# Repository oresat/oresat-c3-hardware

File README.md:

# oresat-c3
## General information
This is the C3 (Command, Communication, and Control) card for OreSat. It acts as the central control point for the entire OreSat project, provides
telemetry to the ground, and receiver commands. It's the "on board computer" (OBC) of the OreSat bus. It has:

- Octavo OSD335x-SM SIP AM335X-based Cortex A8 Microporcessor
- On Semi AX5043-based L Band (1.265 GHz) receiver
- On Semi AX5043-based UHF Band (436.5 MHz) receiver and transmitter with 1W PA.
- Custom radiation tolerant watchdog timer based on the TI TLV1042 comparator.
- 16 GB eMMC flash data storage
- 1 Mbit of FRAM for high reliability state and variable storage
- Supercapacitor-backed up RTC
- Two antenna deployment circuits
- OreSat Power Domain (OPD) control circuitry

Design materials are on Google docs; we'll post links / PDFs soon.

Bill of Materials (BOM) can be found [here](https://docs.google.com/spreadsheets/d/11vG1kWyrAjmbF5QJM-EhXmvQoF6O47japwYlHF802do/edit#gid=1239769296).

## OreSat C3 version 6 (KiCAD)

Fixes for the radio receivers, version 2 backplane pinout, and lots of little tweaks
after our lessons learned on OreSat0. OH, and a COMPLETE REFACTOR since we switched from
the STM32F439 to an Octavo OSD335x-SM and switched from EAGLE to KICAD. Yikes.

### V6 Software

The C3 runs Python code that interacts with the radios, peripherals, and CAN bus. [Here's more information](https://github.com/oresat/oresat-c3-software).

## OreSat C3 version 5 (EAGLE)

C3 V5 flew on Oresat0, Oregon's first satellite! Everything worked great, except for the
radio receivers (L band LNA oscillated, and UHF LNA was turned off in firmware).

### v5 Firmware

The firmware for the C3 card is written in C and runs on top of ChibiOS, a small RTOS.
It is integrated into the [oresat-firmware](https://github.com/oresat/oresat-firmware) repository.
The firmware application for this project is located
[here](https://github.com/oresat/oresat-firmware/tree/c3_capstone/src/f4/app_c3_v1).

## OreSat C3 version 4 (EAGLE)

C3 V4 is our latest version of the C3 card; it's getting ready for flight in 
Q2 2021 in OreSat0. It's got all of the functionality necessary for flight.

## OreSat C3 V3 (2019-2020 ECE Capstone)

The 2018-2019 ECE Capstone brought the card to version 3. It implements an
STM32F446VET6 IC, the full L band receiver with ultistage LNA, and a UHF radio 
with LNA but no PA for transmitting.

## Breadboard Prototype

Most embedded project starts out as a bunch of development boards strung together;
the C3 is no different! The breadboard prototype for the C3 card implements an
STM32F446RE development board connected to two SPI radios, the OreSat
FlatSat backplane via a CAN transceiver and I2C for the OPD interface,
and a SDIO and SPI connected SD/MMC Card. The breadboard implements
stronger pullups for the I2C lines than the GPIO of the STM32 can
provide. It is currently capable of interfacing with and activating the
OPD connected boards.

## License

All materials in this repo are copyright Portland State Aerospace Society and are licensed under the CERN Open Hardware Licence Version 2 -
Strongly Reciprocal (CERN-OHL-S v2), or any later version. A copy of the license is located in [here](LICENSE.md).

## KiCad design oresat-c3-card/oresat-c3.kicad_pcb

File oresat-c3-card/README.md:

---
title: "**OreSat C3 Card**"
subtitle: |
  **Fabrication and Assembly Information**\
  For build TIME-STAMP
fontsize: 10pt
geometry:
  - margin=0.5in
toc: true
toc-depth: 2
colorlinks: true
urlcolor: blue
---

\newpage

# About this Board

## Board Description

The C3 ("Command, Control, and Communications") card is the main on-board computer (OBC) / housekeeping unit (HKU) / Command and Data Handling (CDH) subsystem for the open source [OreSat CubeSat system](https://www.oresat.org/). The C3 card:

- Connects to the backplane with a main connector and two RF ports
- Has an L band radio receiver based on the AT86RF215.
- Has a UHF radio transceiver based on the AT86RF215
- Has a radiation tolerant watchdog timer (with a cheap commercial replacement if you're not going to orbit)
- Controls the OreSat Power Domain (OPD), which turns on and off and controls other cards
- Talks to both CAN OreSat CAN busses

## Documentation Links

- C3 hardware Git repository: <https://github.com/oresat/oresat-c3-hardware>
- C3 software Git reposity: <https://github.com/oresat/oresat-c3-software>
- **TODO:** C3 Design Notes + Design Review Notes

## Documentation Files

| Filename                        | Notes                                    |
| ------------------------------- | ---------------------------------------- |
| README.pdf                      | This README file                         |
| PROJECT-NAME-outline.dxf        | Board outline (with holes) in DXF format |
| PROJECT-NAME-pcba.step          | 3D model of PCBA (with components)       |
| PROJECT-NAME-render-bot.jpg     | Render of the top of the 3D model        |
| PROJECT-NAME-render-bot.jpg     | Render of the bottom of the 3D model     |
| PROJECT-NAME-schematic.pdf      | PDF of board schematics                  |

## Contact Information

- Website: <https://www.oresat.org/>
- Email: <oresat@pdx.edu>
- Instagram: @pdxaerospace

## Board Renders

{width=50%}
{width=50%}

\newpage

# Printed Circuit Board (PCB) Fabrication Information

## Board Info

- 4 layer board
- Bounding box is 99.8 x 94.6 mm (3.93 x 3.72 in)
- Board thickness is 1.59 mm (0.063 inch)
- **Important:** See Materials and Stack Up sections below

## Board Requirements

- Design Rules
    - Minimum Trace / Space design rules
       - Outer layers: 0.127 mm (5.0 mil) / 0.127 mm (5.0 mil)
       - Inner layers: 0.127 mm (5.0 mil) / 0.127 mm (5.0 mil)
    - Outer dimension router tolerance: +/- 0.254 mm (10.0 mil)
    - Hole placement tolerance: +/- 0.075 mm (3.0 mil)
    - Inner tab routed slot tolerance: +/- 0.254 mm (10.0 mil)
- Drills
   - Drill Positional Tolerance: 0.051 mm (2.0 mil)
   - Drill Size tolerance: +/- 0.064 mm (2.5 mil)
- Plated/Un-plated holes
  - There are 6 un-plated (NPT) holes
  - There are 1477 plated through (PTH) holes
  - PTH minimum diameter: 0.254 mm (10 mil)
  - PTH minimum annulus: 0.102 mm (4 mil) radius
- Outline/Routing
  - Requires a 1.0 mm or smaller diameter routing bit
- Slots
  - There are no slots.
- Cutouts
  - There are no cutouts
- There are 3 fiducials on the top layer.
- Panel tabs ("mouse bites")
   - Card edges must be smooth; no mouse bites or other intrusions into the card outline.
   - If external mouse bites are required, minimize and customer will remove by hand before assembly.
- If not otherwise specified, build to IPC 6012 Class 2 or better.

## Materials

- Controlled impedance
   - The stackup is critical for the performance of high speed signals on this board.
   - As long as the stackup is controlled, the board is not considered controlled impedance.
- Isola FR408HR or material with equivalent Dk.
- Board Surface treatment should be ENIG, althogh immersion Silver is acceptable.
- White silkscreen on top and bottom surface
- Taiyo PSR-4000 or equivalent soldermask on top and bottom, no requirements for color.

## Stack Up

| Layer         | Thickness           | Notes                                        |
|---------------|---------------------|----------------------------------------------|
| Top Copper    | 0.043 mm /  1.7 mil |  Layer 1 foil, 1 oz Cu after plating         |
| prepreg       | 0.200 mm /  7.9 mil |  Prepreg - Isola FR408HR 2113                |
| Layer 2       | 0.018 mm /  0.7 mil |  Layer 2 foil, 0.5 oz Cu                     |
| Core          | 0.991 mm /   39 mil |  Core Isola FR408HR                          |
| Layer 3       | 0.018 mm /  0.7 mil |  Layer 3 foil, 0.5 oz Cu                     |
| prepreg       | 0.200 mm /  7.9 mil |  Prepreg - Isola FR408HR 2113                |
| Bottom Copper | 0.043 mm /  1.7 mil |  Layer 4 foil, 1 oz copper after plating     |
| **Total Stackup** | **1.588 mm / 62.5 mil** |                                      |

## Array / Panel Information

- Coordinate with Contract Manufacturer (CM) for optimal size of this panel.
- If no feedback from CM, then produce single boards (no panel).

## Fabrication Files

### IPC-2581 File

| Filename                 | Notes                                   |
| ------------------------ | --------------------------------------- |
| PROJECT-NAME-ipc2581.xml | IPC-2581 board information file         |

### Legacy PCB Files

| Filename                      | Notes                                         |
| ------------------------------| --------------------------------------------- |
| PROJECT-NAME-Edge_Cuts.gbr    | RS274X file for the dimension (outline) layer |
| PROJECT-NAME-F_Silkscreen.gbr | RS274X file for the top silkscreen            |
| PROJECT-NAME-F_Mask.gbr       | RS274X file for the top soldermask            |
| PROJECT-NAME-F_Cu.gbr         | RS274X file for the top copper layer          |
| PROJECT-NAME-In1_Cu.gbr       | RS274X file for the layer 2 copper            |
| PROJECT-NAME-In2_Cu.gbr       | RS274X file for the layer 3 copper            |
| PROJECT-NAME-B_Cu.gbr         | RS274X file for the bottom copper layer       |
| PROJECT-NAME-B_Mask.gbr       | RS274X file for the bottom soldermask         |
| PROJECT-NAME-B_Silkscreen.gbr | RS274X file for the bottom silkscreen         |
| PROJECT-NAME-NPTH.drl         | Excellon file for non-plated through holes    |
| PROJECT-NAME-PTH.drl          | Excellon file for plated through holes        | 

\newpage

# Printed Circuit Board Assembly (PCBA) Information

## Assembly Info

- All components are on the top side of the board.
- This PCBA is mostly surface mount (SMT) with a few (THT) components.

## Assembly Requirements

- Assemble to IPC Class 2 or better
- Bake components that are not moisture sealed to appropriate levels as required.
- Solder paste MUST be leaded.
- Aqueous flux and wash strongly preferred.
   - Clean to NASA Standard "Visibly Clean (VC)": No particles or residues are visible to the naked eye.
- No conformal coating.
- Ship in antistatic protective bag

## Component Specific Assembly Information

- SMPM connectors (J3, J4) should be hand-added (there is no solder paste for their footprints).
- U1 and U28 are extremely expensive ($75 and $150 ea, respectively).
- U15 and U21 are EOL and will be supplied in cut tape form.

## Assembly Files

### IPC-2581 File

| Filename                 | Notes                           |
| ------------------------ | ------------------------------- |
| PROJECT-NAME-ipc2581.xml | IPC-2581 board information file |

### Bill of Materials (BOM)

| Filename             | Description                            |
| -------------------- | -------------------------------------- |
| PROJECT-NAME-bom.csv | BOM in Comma Separated Variable format |

### Solder Paste Stencils

| Filename                 | Notes                                            |
| ------------------------ | ------------------------------------------------ |
| PROJECT-NAME-B_Paste.gbr | RS274X file for top/front solder paste stencil   |
| PROJECT-NAME-F_Paste.gbr | RS274X file for bottom/back solder paste stencil |

### Mounting/Placement Location

| Filename            | Description                                 |
| ------------------- | ------------------------------------------- |
| PROJECT-NAME-3u.pos | Pick and place locations for components     |

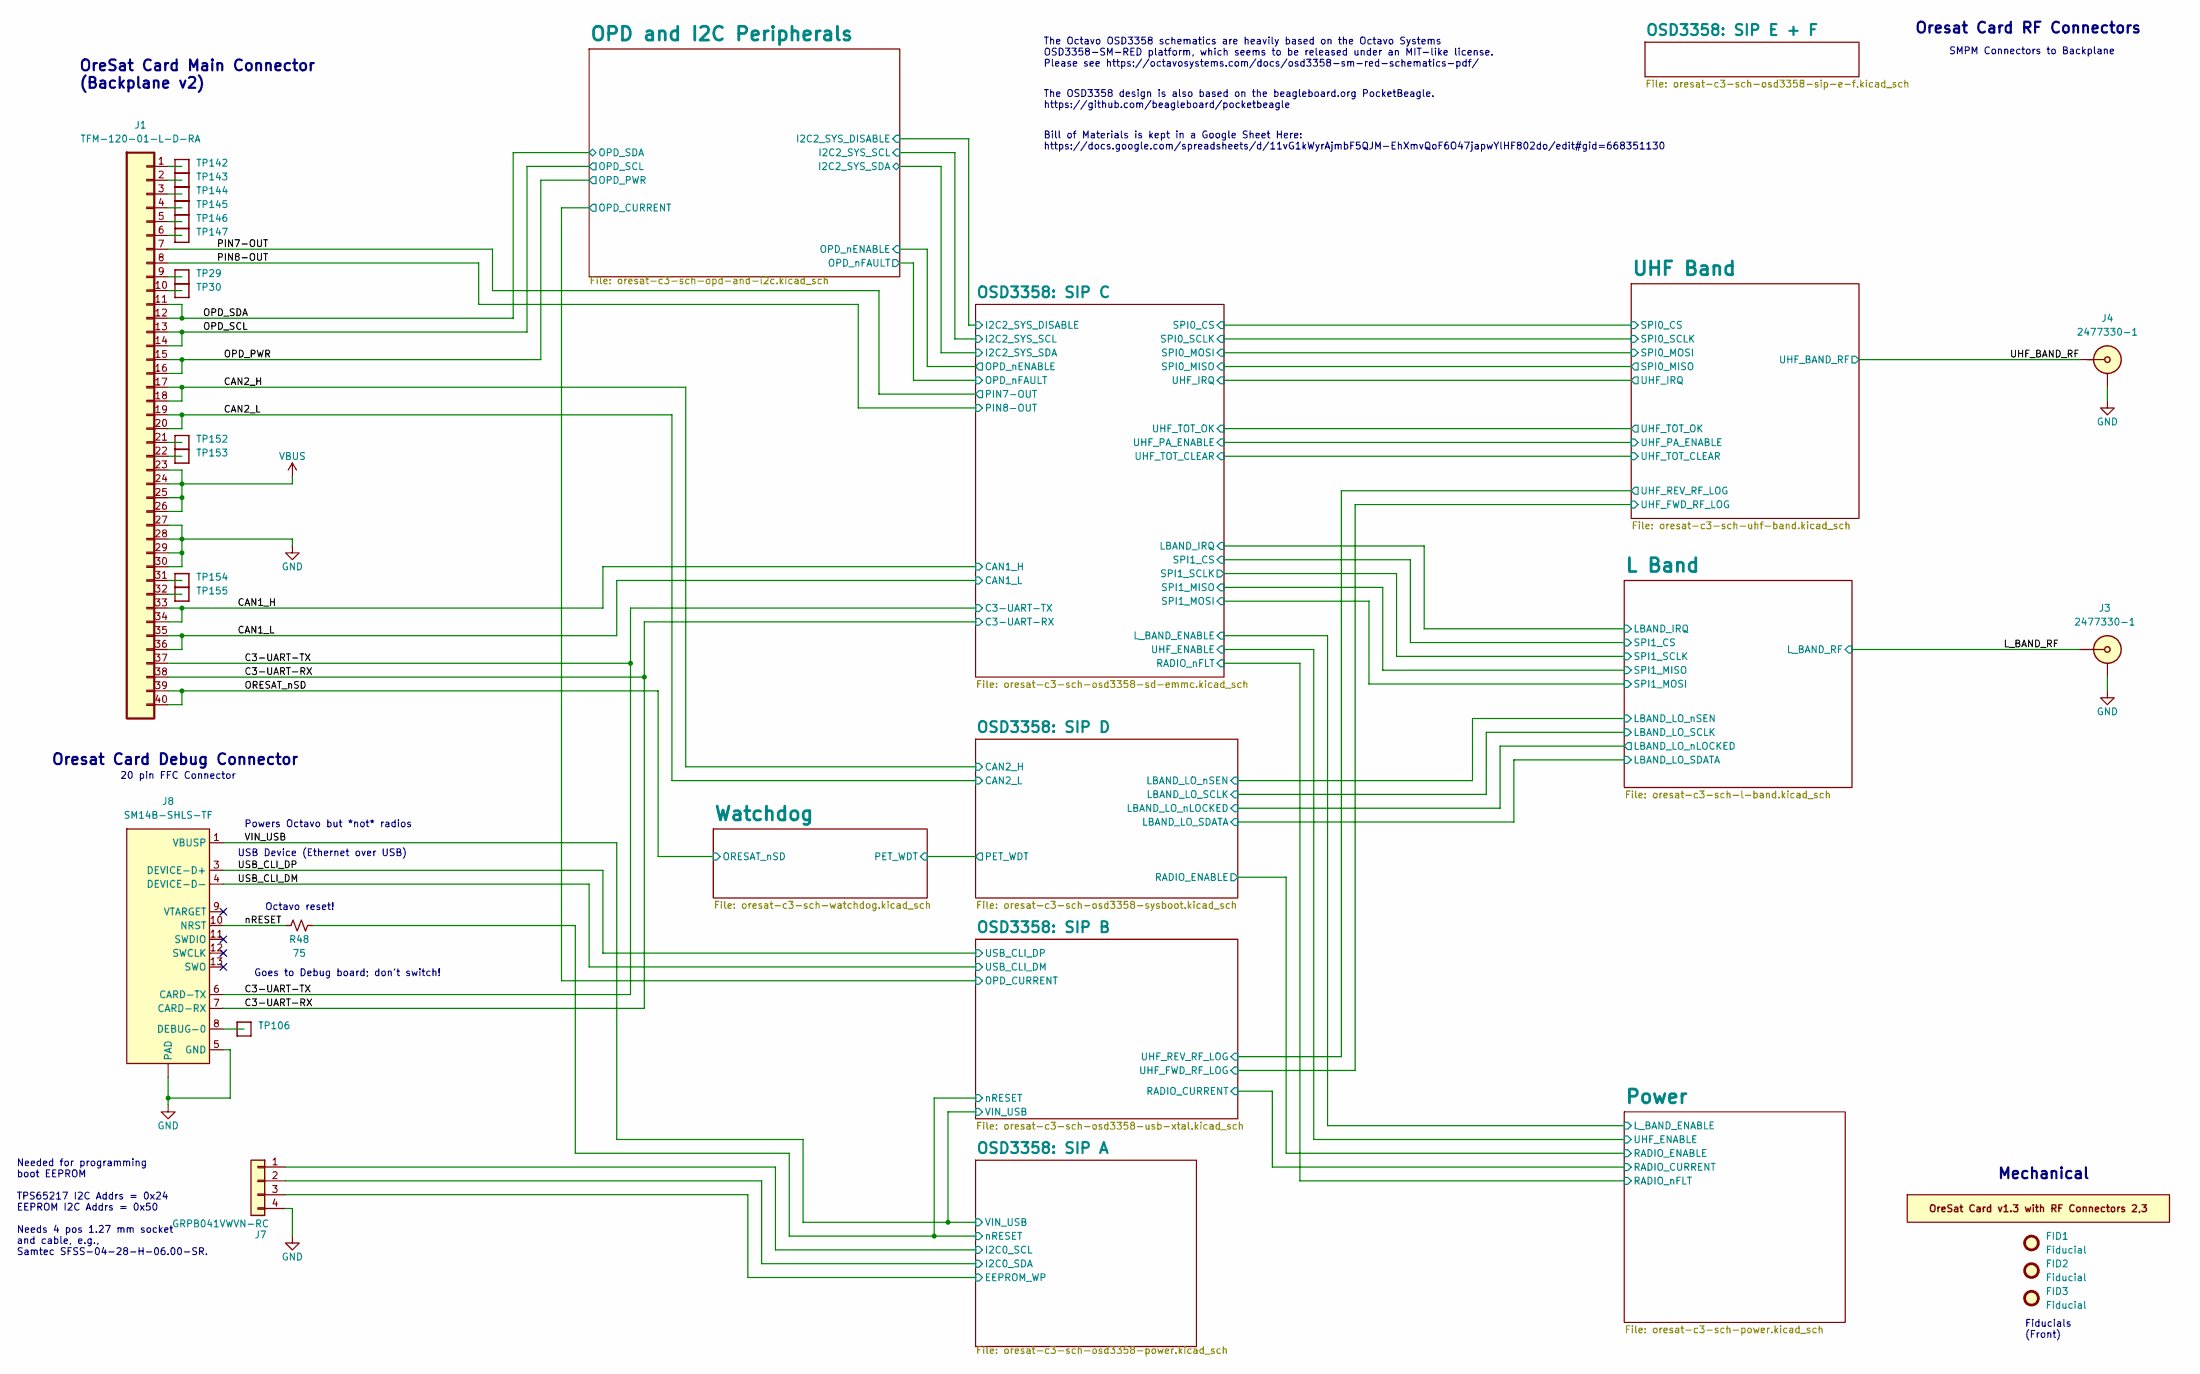
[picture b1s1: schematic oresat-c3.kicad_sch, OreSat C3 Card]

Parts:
FID1, FID2, FID3: Fiducial; Fiducial_1mm_Mask2mm
J1: TFM-120-01-L-D-RA; J-SAMTEC-TFM-120-X1-XXX-D-RA; MPN TFM-120-01-L-D-RA
J3, J4: 2477330-1; J-MOLEX-SMPM-073300-002X; MPN 2477330-1
J7: GRPB041VWVN-RC; PinHeader_1x04_P1.27mm_Vertical; MPN GRPB041VWVN-RC
J8: SM14B-SHLS-TF; J-JST-SM14BSHLSTF; MPN SM14B-SHLS-TF
PCB1: ORESAT-CARD-V1.3-GENERIC-1RF-POS2; ORESAT-CARD-V1.3-2RF-RIGHT; MPN N/A
R48: 75; 0603-C-NOSILK; MPN RMCF0603FT75R0
TP29, TP30, TP106, TP142, TP143, TP144, TP145, TP146, TP147, TP152, TP153, TP154, TP155: Test-Point; TestPoint_Pad_D1.0mm

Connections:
/C3-UART-RX: J1.38, J8.7 (CARD-RX); also elsewhere on the board
/C3-UART-TX: J1.37, J8.6 (CARD-TX); also elsewhere on the board
/CAN1_H: J1.33, J1.34; also elsewhere on the board
/CAN1_L: J1.35, J1.36; also elsewhere on the board
/CAN2_H: J1.17, J1.18; also elsewhere on the board
/CAN2_L: J1.19, J1.20; also elsewhere on the board
/L_BAND_RF: J3.1 (SIG_SIG); also elsewhere on the board
/OPD_PWR: J1.15, J1.16; also elsewhere on the board
/OPD_SCL: J1.13, J1.14; also elsewhere on the board
/OPD_SDA: J1.11, J1.12; also elsewhere on the board
/ORESAT_nSD: J1.39, J1.40; also elsewhere on the board
/OSD3358: SIP A/EEPROM_WP: J7.3; also elsewhere on the board
/OSD3358: SIP A/I2C0_SCL: J7.1; also elsewhere on the board
/OSD3358: SIP A/I2C0_SDA: J7.2; also elsewhere on the board
/OSD3358: SIP A/nRESET: R48.2; also elsewhere on the board
/PIN7-OUT: J1.7; also elsewhere on the board
/PIN8-OUT: J1.8; also elsewhere on the board
/UHF_BAND_RF: J4.1 (SIG_SIG); also elsewhere on the board
/USB_CLI_DM: J8.4 (DEVICE-D-); also elsewhere on the board
/USB_CLI_DP: J8.3 (DEVICE-D+); also elsewhere on the board
/VIN_USB: J8.1 (VBUSP), J8.2 (VBUSP); also elsewhere on the board
/nRESET: J8.10 (NRST), R48.1
GND: J1.27, J1.28, J1.29, J1.30, J3.2 (SHLD_SHLD), J3.SHLD, J4.2 (SHLD_SHLD), J4.SHLD, J7.4, J8.5 (GND), J8.14 (GND), J8.15 (PAD), J8.16 (PAD); also elsewhere on the board
unnamed: J1.1, TP142.1 (1_1)
unnamed: J1.2, TP143.1 (1_1)
unnamed: J1.3, TP144.1 (1_1)
unnamed: J1.4, TP145.1 (1_1)
unnamed: J1.5, TP146.1 (1_1)
unnamed: J1.6, TP147.1 (1_1)
unnamed: J1.9, TP29.1 (1_1)
unnamed: J1.10, TP30.1 (1_1)
unnamed: J1.21, TP152.1 (1_1)
unnamed: J1.22, TP153.1 (1_1)
unnamed: J1.31, TP154.1 (1_1)
unnamed: J1.32, TP155.1 (1_1)
unnamed: J8.8 (DEBUG-0), TP106.1 (1_1)
VBUS: J1.23, J1.24, J1.25, J1.26; also elsewhere on the board

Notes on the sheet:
Bill of Materials is kept in a Google Sheet Here: https://docs.google.com/spreadsheets/d/11vG1kWyrAjmbF5QJM-EhXmvQoF6O47japwYlHF802do/edit#gid=668351130
The Octavo OSD3358 schematics are heavily based on the Octavo Systems OSD3358-SM-RED platform, which seems to be released under an MIT-like license. Please see https://octavosystems.com/docs/osd3358-sm-red-schematics-pdf/
OreSat Card Main Connector (Backplane v2)
Mechanical
Needed for programming boot EEPROM TPS65217 I2C Addrs = 0x24 EEPROM I2C Addrs = 0x50 Needs 4 pos 1.27 mm socket and cable, e.g., Samtec SFSS-04-28-H-06.00-SR.
Octavo reset!
20 pin FFC Connector
Oresat Card RF Connectors
Oresat Card Debug Connector
Goes to Debug board; don't switch!
Powers Octavo but *not* radios
The OSD3358 design is also based on the beagleboard.org PocketBeagle. https://github.com/beagleboard/pocketbeagle
USB Device (Ethernet over USB)
SMPM Connectors to Backplane
Fiducials (Front)

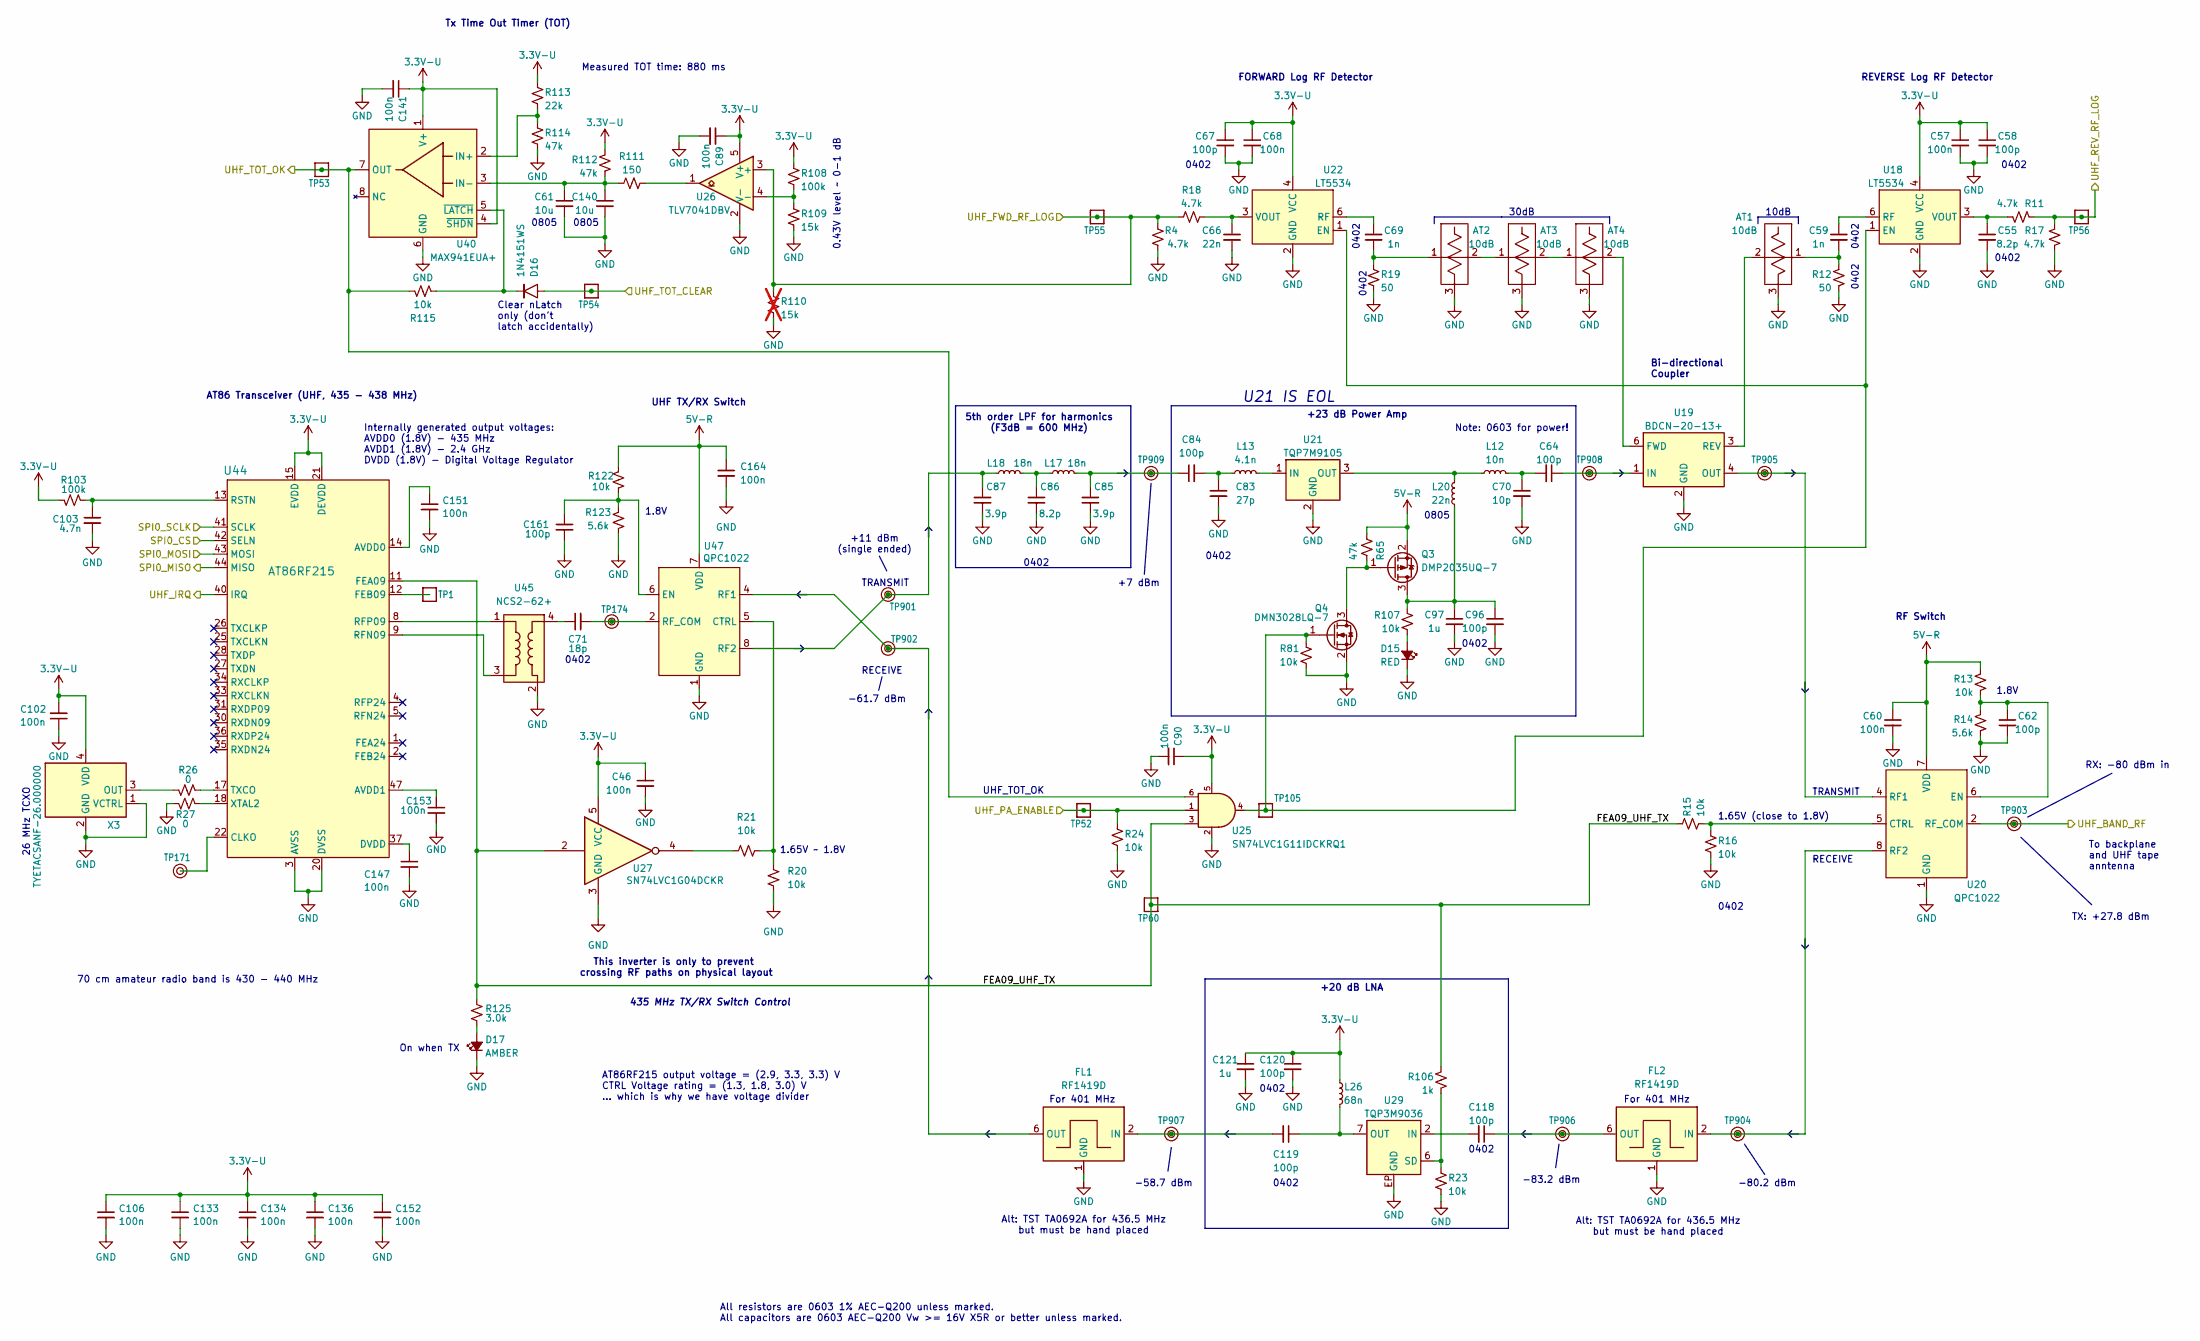
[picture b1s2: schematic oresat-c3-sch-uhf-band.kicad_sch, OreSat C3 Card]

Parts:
AT1, AT2, AT3, AT4: 10dB; PAT0816(0603); MPN PAT0816-C-10DB-T5
C46, C57, C60, C68, C89, C90, C102, C106, C133, C134, C136, C141, C147, C151, C152, C153, C164: 100n; 0603-C-NOSILK; MPN C0603C104K5RACAUTO
C55, C86: 8.2p; 0402-B-NOSILK; MPN GCQ1555C1H8R2BB01D
C58, C67, C84, C96, C118, C119, C120: 100p; 0402-B-NOSILK; MPN C0402C101J5GACAUTO
C59, C69: 1n; 0402-B-NOSILK; MPN C0402C102J3GACAUTO
C61, C140: 10u; 0805-C-NOSILK; MPN GRT21BC71E106KE13K
C62, C64, C161: 100p; 0603-C-NOSILK; MPN C0603C101K5HACAUTO
C66: 22n; 0603-C-NOSILK; MPN C0603C223K1RACAUTO
C70: 10p; 0603-C-NOSILK; MPN C0603C100J1GACAUTO
C71: 18p; 0402-B-NOSILK; MPN CBR04C180J5GACAUTO
C83: 27p; 0402-B-NOSILK; MPN C0402C270J5GACAUTO
C85, C87: 3.9p; 0402-B-NOSILK; MPN GCQ1555C1H3R9WB01D
C97, C121: 1u; 0603-C-NOSILK; MPN GRT188R71E105KE13D
C103: 4.7n; 0603-C-NOSILK; MPN C0603C472K5RACAUTO
D15: RED; LED_0603_1608Metric; MPN 150060RS75000
D16: 1N4151WS; D_SOD-323; MPN 1N4151WS-E3-08
D17: AMBER; LED_0603_1608Metric; MPN 150060AS75000
FL1, FL2: RF1419D; Filter_SAW-8_3.8x3.8mm; MPN RF1419D
L12: 10n; L_0603_1608Metric; MPN LQW18AN10NG00D
L13: 4.1n; L_0402_1005Metric; MPN LQW15AN4N1B00D
L17, L18: 18n; L_0402_1005Metric; MPN 0402HP-18NXGL
L20: 22n; L_0805_2012Metric; MPN LQW2BAN22NG00L
L26: 68n; L_0603_1608Metric; MPN LQW18AN68NG8ZD
Q3: DMP2035UQ-7; SOT-23; MPN DMP2035UQ-7
Q4: DMN3028LQ-7; SOT-23-3; MPN DMN3028LQ-7
R4, R11, R17, R18: 4.7k; 0603-C-NOSILK; MPN RMCF0603FT4K70
R12, R19: 50; 0402-B-NOSILK; MPN CH0402-50RJNPA
R13, R15, R16, R20, R21, R23, R24, R81, R107, R115, R122: 10k; 0603-C-NOSILK; MPN RMCF0603FT10K0
R14, R123: 5.6k; 0603-C-NOSILK; MPN RMCF0603FT5K60
R26, R27: 0; 0603-C-NOSILK; MPN RMCF0603ZT0R00
R65, R112, R114: 47k; 0603-C-NOSILK; MPN RMCF0603FT47K0
R103, R108: 100k; 0603-C-NOSILK; MPN RMCF0603FT100K
R106: 1k; 0603-C-NOSILK; MPN RMCF0603FT1K00
R109: 15k; 0603-C-NOSILK; MPN RMCF0603FT15K0
R110: 15k; R_0603_1608Metric; not fitted
R111: 150; 0603-C-NOSILK; MPN RMCF0603FT150R
R113: 22k; 0603-C-NOSILK; MPN RMCF0603FT22K0
R125: 3.0k; 0603-C-NOSILK; MPN RMCF0603FT3K00
TP1, TP52, TP53, TP54, TP55, TP56, TP60, TP105: Test-Point; TestPoint_Pad_D1.0mm
TP171, TP174, TP901, TP902, TP903, TP904, TP905, TP906, TP907, TP908, TP909: TestPoint_RF_Probe
U18, U22: LT5534; SOT-363_SC-70-6; MPN LT5534ESC6#TRPBF
U19: BDCN-20-13+; MPN BDCN-20-13+
U20, U47: QPC1022; MPN QPC1022TR7
U21: TQP7M9105; U-QORVO-TQP7M9105-VIAS; MPN TQP7M9105
U25: SN74LVC1G11IDCKRQ1; Texas_R-PDSO-G6; MPN SN74LVC1G11IDCKRQ1
U26: TLV7041DBV; SOT-23-5; MPN TLV7041DBVR
U27: SN74LVC1G04DCKR; SOT-353_SC-70-5; MPN SN74LVC1G04QDCKRQ1
U29: TQP3M9036; U-Qorvo-TQP3M9036-QFN-8-MO-220E; MPN TQP3M9036
U40: MAX941EUA+; LINEAR-MSOP-8-AND-MAXIM-UMAX-8-21-0036; MPN MAX941EUA+
U44: AT86RF215; QFN-48-1EP_7x7mm_P0.5mm_EP5.6x5.6mm; MPN AT86RF215-ZUR
U45: NCS2-62+; 2450FB15A050E_JOT; MPN NCS2-62+
X3: TYETACSANF-26.000000; X_TCXO_SMD_Taitien_2.5x2.0mm; MPN TYETACSANF-26.000000

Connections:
3.3V-U: C46.1, C57.1, C58.1, C67.1, C68.1, C89.1, C90.1, C102.2, C106.1, C120.1, C121.1, C133.1, C134.1, C136.1, C141.1, C152.1, L26.1, R103.2, R108.1, R112.1, R113.1, U18.4 (VCC), U22.4 (VCC), U25.5, U26.5 (V+), U27.5 (VCC), U40.1 (V+), U40.4 (~SHDN), U44.15 (EVDD), U44.21 (DEVDD), U44.29 (DEVDD), U44.39 (DEVDD), U44.46 (EVDD), X3.4 (VDD); also elsewhere on the board
5V-R: C60.1, C164.1, Q3.2 (S), R13.1, R65.1, R122.1, U20.7 (VDD), U47.7 (VDD); also elsewhere on the board
/OSD3358: SIP B/UHF_FWD_RF_LOG: R4.1, R18.1, R110.1, TP55.1 (1_1), U26.3 (+); also elsewhere on the board
/OSD3358: SIP B/UHF_REV_RF_LOG: R11.1, R17.1, TP56.1 (1_1); also elsewhere on the board
/OSD3358: SIP C/SPI0_CS: U44.42 (SELN); also elsewhere on the board
/OSD3358: SIP C/SPI0_MISO: U44.44 (MISO); also elsewhere on the board
/OSD3358: SIP C/SPI0_MOSI: U44.43 (MOSI); also elsewhere on the board
/OSD3358: SIP C/SPI0_SCLK: U44.41 (SCLK); also elsewhere on the board
/OSD3358: SIP C/UHF_IRQ: U44.40 (IRQ); also elsewhere on the board
/OSD3358: SIP C/UHF_PA_ENABLE: R24.1, TP52.1 (1_1), U25.1; also elsewhere on the board
/OSD3358: SIP C/UHF_TOT_CLEAR: D16.2, TP54.1 (1_1); also elsewhere on the board
/OSD3358: SIP C/UHF_TOT_OK: R115.1, TP53.1 (1_1), U25.6, U40.7 (OUT); also elsewhere on the board
/UHF Band/FEA09_UHF_TX: R15.1, R106.1, R125.1, TP60.1 (1_1), U25.3, U27.2, U44.11 (FEA09)
/UHF_BAND_RF: TP903.1 (1_1), U20.2 (RF_COM); also elsewhere on the board
GND: AT1.3, AT2.3, AT3.3, AT4.3, C46.2, C55.2, C57.2, C58.2, C60.2, C61.2, C62.2, C66.2, C67.2, C68.2, C70.2, C83.2, C85.2, C86.2, C87.2, C89.2, C90.2, C96.2, C97.2, C102.1, C103.2, C106.2, C120.2, C121.2, C133.2, C134.2, C136.2, C140.2, C141.2, C147.2, C151.2, C152.2, C153.2, C161.2, C164.2, D15.1 (K), D17.1 (K), FL1.1 (GND), FL1.3 (GND), FL1.4 (GND), FL1.5 (GND), FL1.7 (GND), FL1.8 (GND), FL2.1 (GND), FL2.3 (GND), FL2.4 (GND), FL2.5 (GND), FL2.7 (GND), FL2.8 (GND), Q4.2 (S), R4.2, R12.2, R14.2, R16.2, R17.2, R19.2, R20.1, R23.2, R24.2, R27.2, R81.2, R109.2, R110.2, R114.2, R123.2, U18.2 (GND), U18.5 (GND), U19.2 (GND), U19.5 (GND), U20.1 (GND), U20.3 (GND), U20.9 (GND), U21.2 (GND), U21.EP (GND), U22.2 (GND), U22.5 (GND), U25.2, U26.2 (V-), U27.3 (GND), U29.EP (GND), U40.6 (GND), U44.3 (AVSS), U44.6 (AVSS), U44.7 (AVSS), U44.10 (AVSS), U44.16 (AVSS), U44.19 (AVSS), U44.20 (DVSS), U44.23 (DVSS), U44.24 (DVSS), U44.32 (DVSS), U44.38 (DVSS), U44.45 (AVSS), U44.48 (AVSS), U44.49 (AVSS), U45.2 (GND), U45.6 (GND), U47.1 (GND), U47.3 (GND), U47.9 (GND), X3.1 (VCTRL), X3.2 (GND); also elsewhere on the board
unnamed: AT1.1, C59.2, R12.1
unnamed: AT2.1, C69.2, R19.1
unnamed: AT2.2, AT3.1
unnamed: AT3.2, AT4.1
unnamed: C64.2, C70.1, L12.1
unnamed: C71.1, U45.4
unnamed: C83.1, C84.2, L13.2
unnamed: C84.1, C85.1, L17.1, TP909.1 (1_1)
unnamed: C86.1, L17.2, L18.1
unnamed: D15.2 (A), R107.1
unnamed: D17.2 (A), R125.2
unnamed: C119.2, FL1.2 (IN), TP907.1 (1_1)
unnamed: FL1.6 (OUT), TP902.1 (1_1), U47.4 (RF1)
unnamed: FL2.2 (IN), TP904.1 (1_1), U20.8 (RF2)
unnamed: C118.1, FL2.6 (OUT), TP906.1 (1_1)
unnamed: C96.1, C97.1, L20.2, Q3.3 (D), R107.2
unnamed: Q3.1 (G), Q4.3 (D), R65.2
unnamed: Q4.1 (G), R81.1, TP105.1 (1_1), U18.1 (EN), U22.1 (EN), U25.4
unnamed: R21.2, U27.4
unnamed: R111.2, U26.1
unnamed: C59.1, U18.6 (RF)
unnamed: C55.1, R11.2, U18.3 (VOUT)
unnamed: AT4.2, U19.6 (FWD)
unnamed: C64.1, TP908.1 (1_1), U19.1 (IN)
unnamed: TP905.1 (1_1), U19.4 (OUT), U20.4 (RF1)
unnamed: AT1.2, U19.3 (REV)
unnamed: R15.2, R16.1, U20.5 (CTRL)
unnamed: C62.1, R13.2, R14.1, U20.6 (EN)
unnamed: L13.1, U21.1 (IN)
unnamed: L12.2, L20.1, U21.3 (OUT)
unnamed: C69.1, U22.6 (RF)
unnamed: C66.1, R18.2, U22.3 (VOUT)
unnamed: R108.2, R109.1, U26.4 (-)
unnamed: C118.2, U29.2 (IN)
unnamed: C119.1, L26.2, U29.7 (OUT)
unnamed: R23.1, R106.2, U29.6 (SD)
unnamed: R113.2, R114.1, U40.2 (IN+)
unnamed: C61.1, C140.1, R111.1, R112.2, U40.3 (IN-)
unnamed: D16.1, R115.2, U40.5 (~LATCH)
unnamed: C151.1, U44.14 (AVDD0)
unnamed: C153.1, U44.47 (AVDD1)
unnamed: TP171.1 (1_1), U44.22 (CLKO)
unnamed: C147.1, U44.37 (DVDD)
unnamed: TP1.1 (1_1), U44.12 (FEB09)
unnamed: U44.9 (RFN09), U45.3
unnamed: U44.8 (RFP09), U45.1
unnamed: C103.1, R103.1, U44.13 (RSTN)
unnamed: R26.1, U44.17 (TXCO)
unnamed: R27.1, U44.18 (XTAL2)
unnamed: R20.2, R21.1, U47.5 (CTRL)
unnamed: C161.1, R122.2, R123.1, U47.6 (EN)
unnamed: C87.1, L18.2, TP901.1 (1_1), U47.8 (RF2)
unnamed: C71.2, TP174.1 (1_1), U47.2 (RF_COM)
unnamed: R26.2, X3.3 (OUT)

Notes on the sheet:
AT86 Transceiver (UHF, 435 - 438 MHz)
To backplane and UHF tape anntenna
-80.2 dBm
0402
Alt: TST TA0692A for 436.5 MHz but must be hand placed
-83.2 dBm
+20 dB LNA
Clear nLatch only (don't latch accidentally)
+7 dBm
RECEIVE
RX: -80 dBm in
Tx Time Out Timer (TOT)
AT86RF215 output voltage = (2.9, 3.3, 3.3) V CTRL Voltage rating = (1.3, 1.8, 3.0) V ... which is why we have voltage divider
REVERSE Log RF Detector
For 401 MHz
TRANSMIT
5th order LPF for harmonics (F3dB = 600 MHz)
10dB
0805
-58.7 dBm
26 MHz TCXO
1.65V (close to 1.8V)
U21 IS EOL
Internally generated output voltages: AVDD0 (1.8V) - 435 MHz AVDD1 (1.8V) - 2.4 GHz DVDD (1.8V) - Digital Voltage Regulator
Note: 0603 for power!
Measured TOT time: 880 ms
On when TX
-61.7 dBm
+23 dB Power Amp
30dB
1.8V
1.65V ~ 1.8V
+11 dBm (single ended)
This inverter is only to prevent crossing RF paths on physical layout
UHF_TOT_OK
435 MHz TX/RX Switch Control
70 cm amateur radio band is 430 - 440 MHz
Bi-directional Coupler
RF Switch
0.43V level ~ 0-1 dB

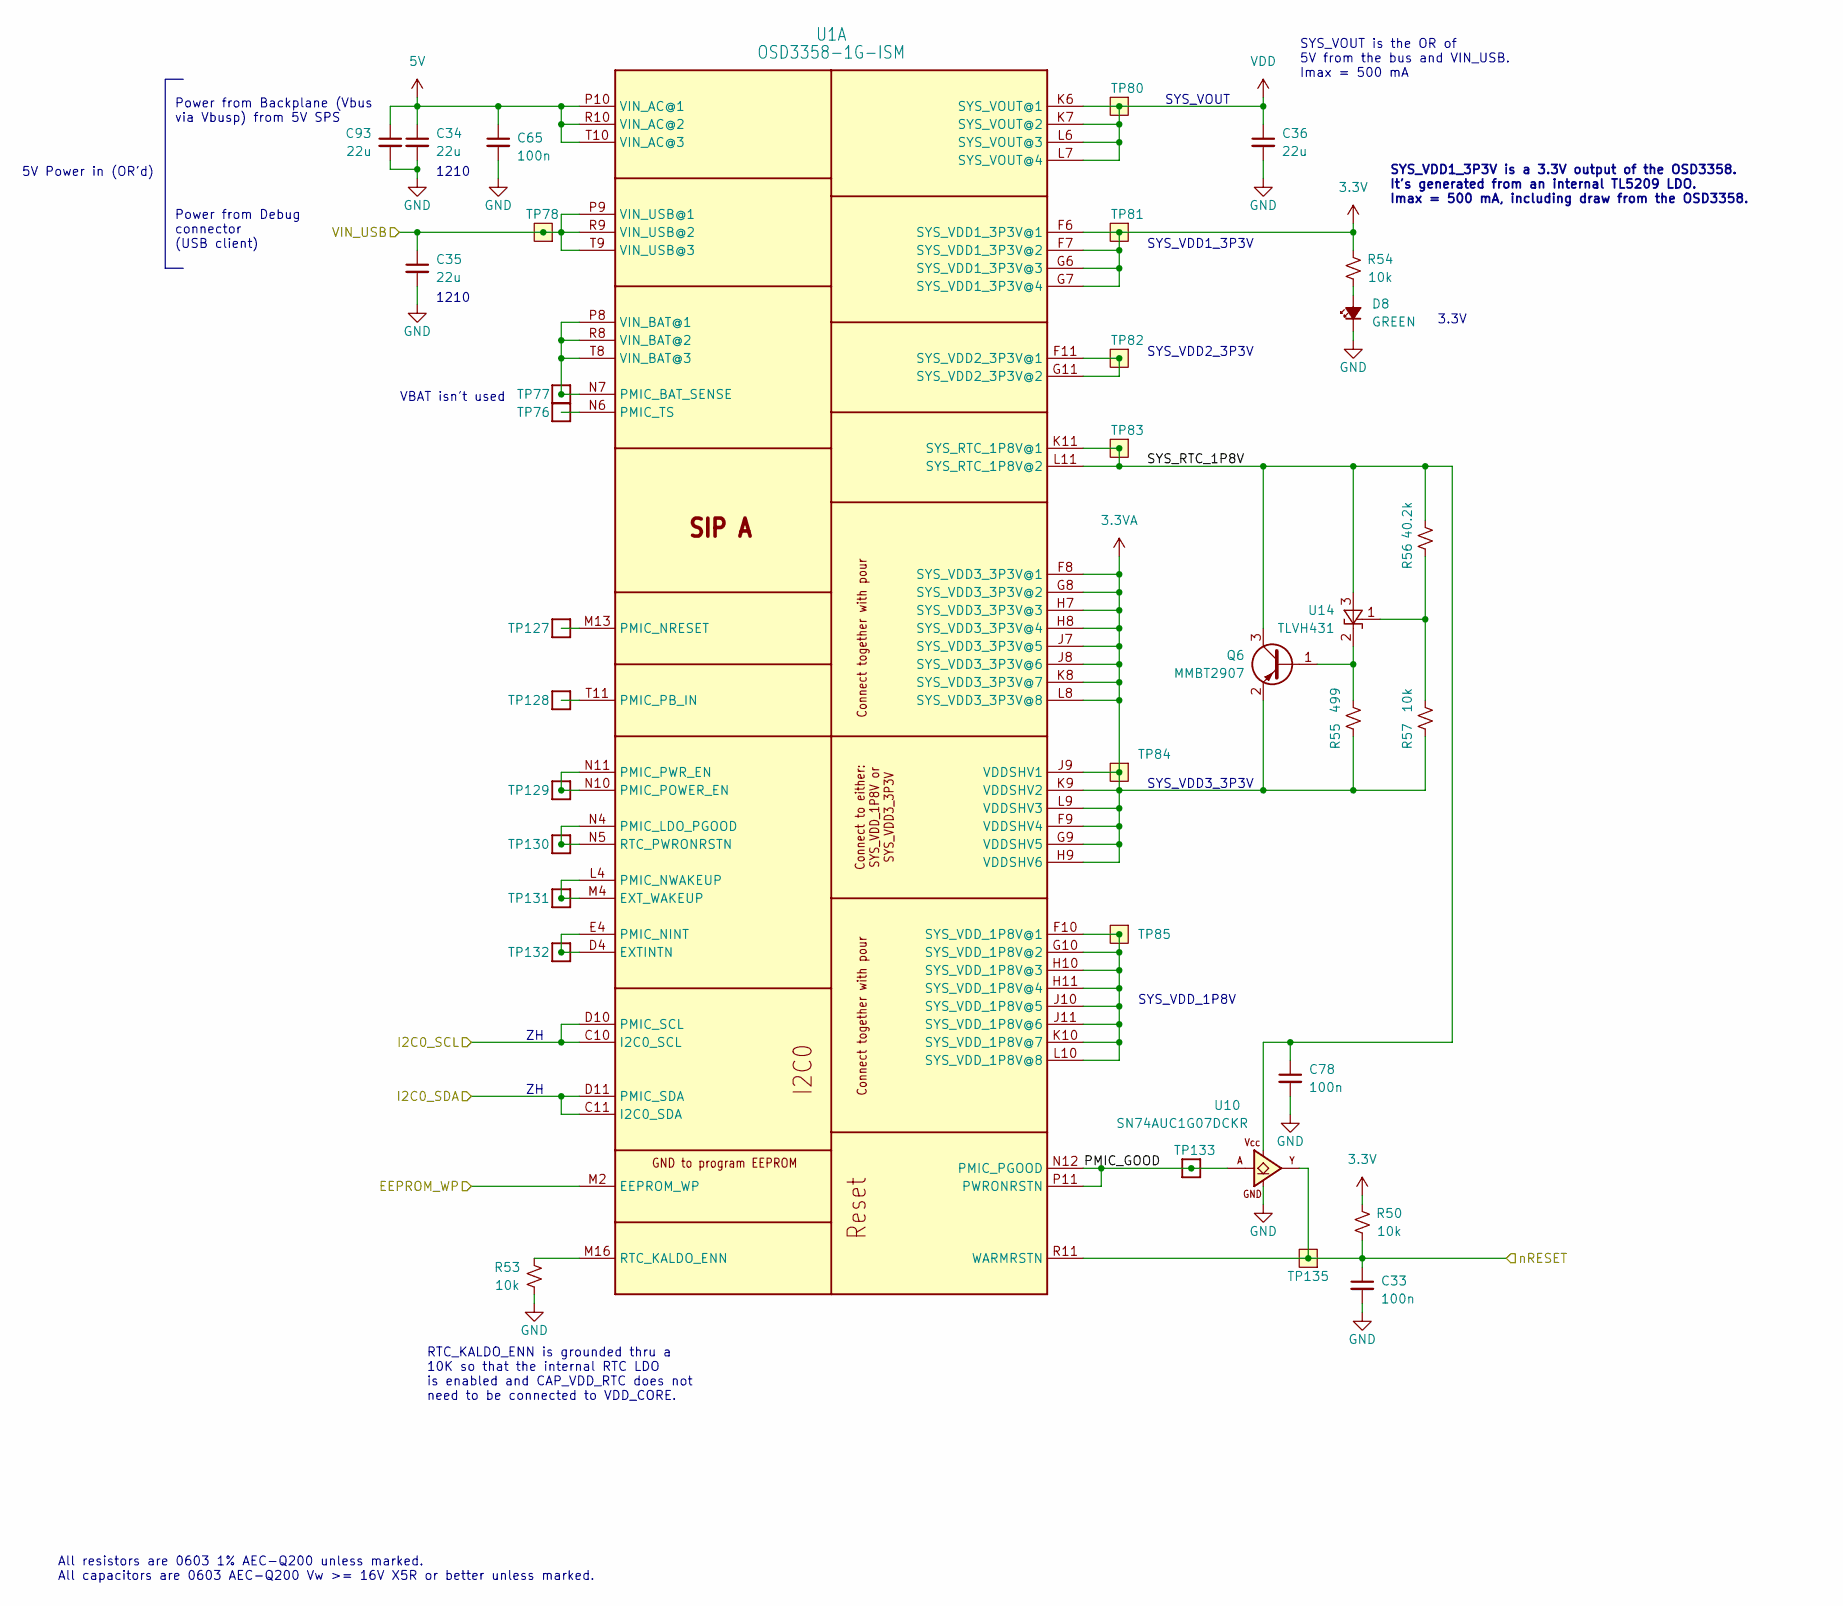
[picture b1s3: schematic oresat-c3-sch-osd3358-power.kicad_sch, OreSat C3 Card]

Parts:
C33, C65, C78: 100n; 0603-C-NOSILK; MPN C0603C104K5RACAUTO
C34, C35, C36, C93: 22u; C_1210_3225Metric; MPN TMK325B7226KMHP
D8: GREEN; LED_0603_1608Metric; MPN 150060GS75000
Q6: MMBT2907; SOT-23; MPN PMBT2907A,215
R50, R53, R54, R57: 10k; 0603-C-NOSILK; MPN RMCF0603FT10K0
R55: 499; 0603-C-NOSILK; MPN RMCF0603FT499R
R56: 40.2k; 0603-C-NOSILK; MPN RMCF0603FT40K2
TP76, TP77, TP127, TP128, TP129, TP130, TP131, TP132, TP133: Test-Point; TestPoint_Pad_D1.0mm
TP78, TP80, TP81, TP82, TP83, TP84, TP85, TP135: Test-Point; TestPoint-0.75mm-th
U1: OSD3358-1G-ISM; U-Octavo-OSD335X-BGA-256; MPN OSD3358-512M-BSM
U10: SN74AUC1G07DCKR; SOT-353_SC-70-5; MPN SN74AUC1G07DCKR
U14: TLVH431; SOT-23; MPN TLVH431BCDBZT

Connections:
3.3V: R50.2, R54.1, TP81.1 (1_1), U1.F6 (SYS_VDD1_3P3V@1), U1.F7 (SYS_VDD1_3P3V@2), U1.G6 (SYS_VDD1_3P3V@3), U1.G7 (SYS_VDD1_3P3V@4); also elsewhere on the board
3.3VA: Q6.2 (E), R55.1, R57.1, TP84.1 (1_1), U1.F8 (SYS_VDD3_3P3V@1), U1.F9 (VDDSHV4), U1.G8 (SYS_VDD3_3P3V@2), U1.G9 (VDDSHV5), U1.H7 (SYS_VDD3_3P3V@3), U1.H8 (SYS_VDD3_3P3V@4), U1.H9 (VDDSHV6), U1.J7 (SYS_VDD3_3P3V@5), U1.J8 (SYS_VDD3_3P3V@6), U1.J9 (VDDSHV1), U1.K8 (SYS_VDD3_3P3V@7), U1.K9 (VDDSHV2), U1.L8 (SYS_VDD3_3P3V@8), U1.L9 (VDDSHV3)
5V: C34.1, C65.1, C93.1, U1.P10 (VIN_AC@1), U1.R10 (VIN_AC@2), U1.T10 (VIN_AC@3); also elsewhere on the board
/OSD3358: SIP A/EEPROM_WP: U1.M2 (EEPROM_WP); also elsewhere on the board
/OSD3358: SIP A/I2C0_SCL: U1.C10 (I2C0_SCL), U1.D10 (PMIC_SCL); also elsewhere on the board
/OSD3358: SIP A/I2C0_SDA: U1.C11 (I2C0_SDA), U1.D11 (PMIC_SDA); also elsewhere on the board
/OSD3358: SIP A/PMIC_GOOD: TP133.1 (1_1), U1.N12 (PMIC_PGOOD), U1.P11 (PWRONRSTN), U10.2 (A)
/OSD3358: SIP A/SYS_RTC_1P8V: C78.1, Q6.3 (C), R56.2, TP83.1 (1_1), U1.K11 (SYS_RTC_1P8V@1), U1.L11 (SYS_RTC_1P8V@2), U10.5 (VCC), U14.3 (A)
/OSD3358: SIP A/nRESET: C33.1, R50.1, TP135.1 (1_1), U1.R11 (WARMRSTN), U10.4 (Y); also elsewhere on the board
/VIN_USB: C35.1, TP78.1 (1_1), U1.P9 (VIN_USB@1), U1.R9 (VIN_USB@2), U1.T9 (VIN_USB@3); also elsewhere on the board
GND: C33.2, C34.2, C35.2, C36.2, C65.2, C78.2, C93.2, D8.1 (K), R53.1, U10.3 (GND); also elsewhere on the board
unnamed: D8.2 (A), R54.2
unnamed: Q6.1 (B), R55.2, U14.2 (K)
unnamed: TP132.1 (1_1), U1.D4 (EXTINTN), U1.E4 (PMIC_NINT)
unnamed: TP131.1 (1_1), U1.L4 (PMIC_NWAKEUP), U1.M4 (EXT_WAKEUP)
unnamed: TP77.1 (1_1), U1.N7 (PMIC_BAT_SENSE), U1.P8 (VIN_BAT@1), U1.R8 (VIN_BAT@2), U1.T8 (VIN_BAT@3)
unnamed: TP130.1 (1_1), U1.N4 (PMIC_LDO_PGOOD), U1.N5 (RTC_PWRONRSTN)
unnamed: TP127.1 (1_1), U1.M13 (PMIC_NRESET)
unnamed: TP128.1 (1_1), U1.T11 (PMIC_PB_IN)
unnamed: TP129.1 (1_1), U1.N10 (PMIC_POWER_EN), U1.N11 (PMIC_PWR_EN)
unnamed: TP76.1 (1_1), U1.N6 (PMIC_TS)
unnamed: R53.2, U1.M16 (RTC_KALDO_ENN)
unnamed: TP82.1 (1_1), U1.F11 (SYS_VDD2_3P3V@1), U1.G11 (SYS_VDD2_3P3V@2)
unnamed: TP85.1 (1_1), U1.F10 (SYS_VDD_1P8V@1), U1.G10 (SYS_VDD_1P8V@2), U1.H10 (SYS_VDD_1P8V@3), U1.H11 (SYS_VDD_1P8V@4), U1.J10 (SYS_VDD_1P8V@5), U1.J11 (SYS_VDD_1P8V@6), U1.K10 (SYS_VDD_1P8V@7), U1.L10 (SYS_VDD_1P8V@8)
unnamed: R56.1, R57.2, U14.1 (REF)
VDD: C36.1, TP80.1 (1_1), U1.K6 (SYS_VOUT@1), U1.K7 (SYS_VOUT@2), U1.L6 (SYS_VOUT@3), U1.L7 (SYS_VOUT@4)

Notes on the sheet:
1210
All resistors are 0603 1% AEC-Q200 unless marked. All capacitors are 0603 AEC-Q200 Vw >= 16V X5R or better unless marked.
SYS_VOUT
SYS_VDD_1P8V
Power from Backplane (Vbus via Vbusp) from 5V SPS
SYS_VDD3_3P3V
SYS_VDD1_3P3V is a 3.3V output of the OSD3358. It's generated from an internal TL5209 LDO. Imax = 500 mA, including draw from the OSD3358.
Power from Debug connector (USB client)
SYS_VDD2_3P3V
SYS_VDD1_3P3V
RTC_KALDO_ENN is grounded thru a 10K so that the internal RTC LDO is enabled and CAP_VDD_RTC does not need to be connected to VDD_CORE.
VBAT isn't used
SYS_VOUT is the OR of 5V from the bus and VIN_USB. Imax = 500 mA
5V Power in (OR'd)
3.3V
